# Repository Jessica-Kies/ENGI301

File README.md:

# ENGI301
Repository for Engi301 coursework

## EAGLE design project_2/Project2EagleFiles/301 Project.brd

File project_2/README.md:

For this project, the template for a PCB for Project 1 was created. The PCB is not going to be printed, this was practice in designing it. 
The first step for this was creating a library. Most of the library is based off the MISC library given by Professor Welsh. Two devices, the PocketBeagle and LED Button were created by me. For the PocketBeagle, the footprint used was created in class. I took the example symbol and split it into two symbols for used and unused ports. The footprint and two symbols were used to create the device. For the LED Button device, I needed to create the footprint and symbol, then the device. The LED Buttons aren’t connected directly to the board, so I just needed to create places for the 4 wires per button to be soldered onto the board. 
After creating the library, the schematics were made. This involved placing all the parts used onto the sheet and connecting the correct pins. The devices included the PocketBeagle, servomotor, hex display, transistor, 4 LED Buttons, buzzer, 6 fiducials, 4 mounting holes, and multiple 1k resistors. One PocketBeagle symbol has all the pins that are connected, while the other has all the unconnected pins. This allowed for better organization on the schematic.
Next, the board layout was done. The board is 4 layers. The middle layers are the ground and power planes. The top layer has the hex display and buzzer since they are visible outside the box. The bottom layer has the PocketBeagle, transistor, LED Buttons, and servomotor. The routing was then done for the layers. Checks were run to make sure there was not interference between parts.
MacroFab Costs for 48-day lead time with parts attached: 1 board: $907.06 	10 boards: $66.945	  100 boards: $26.398 	  1000 boards: $23.034

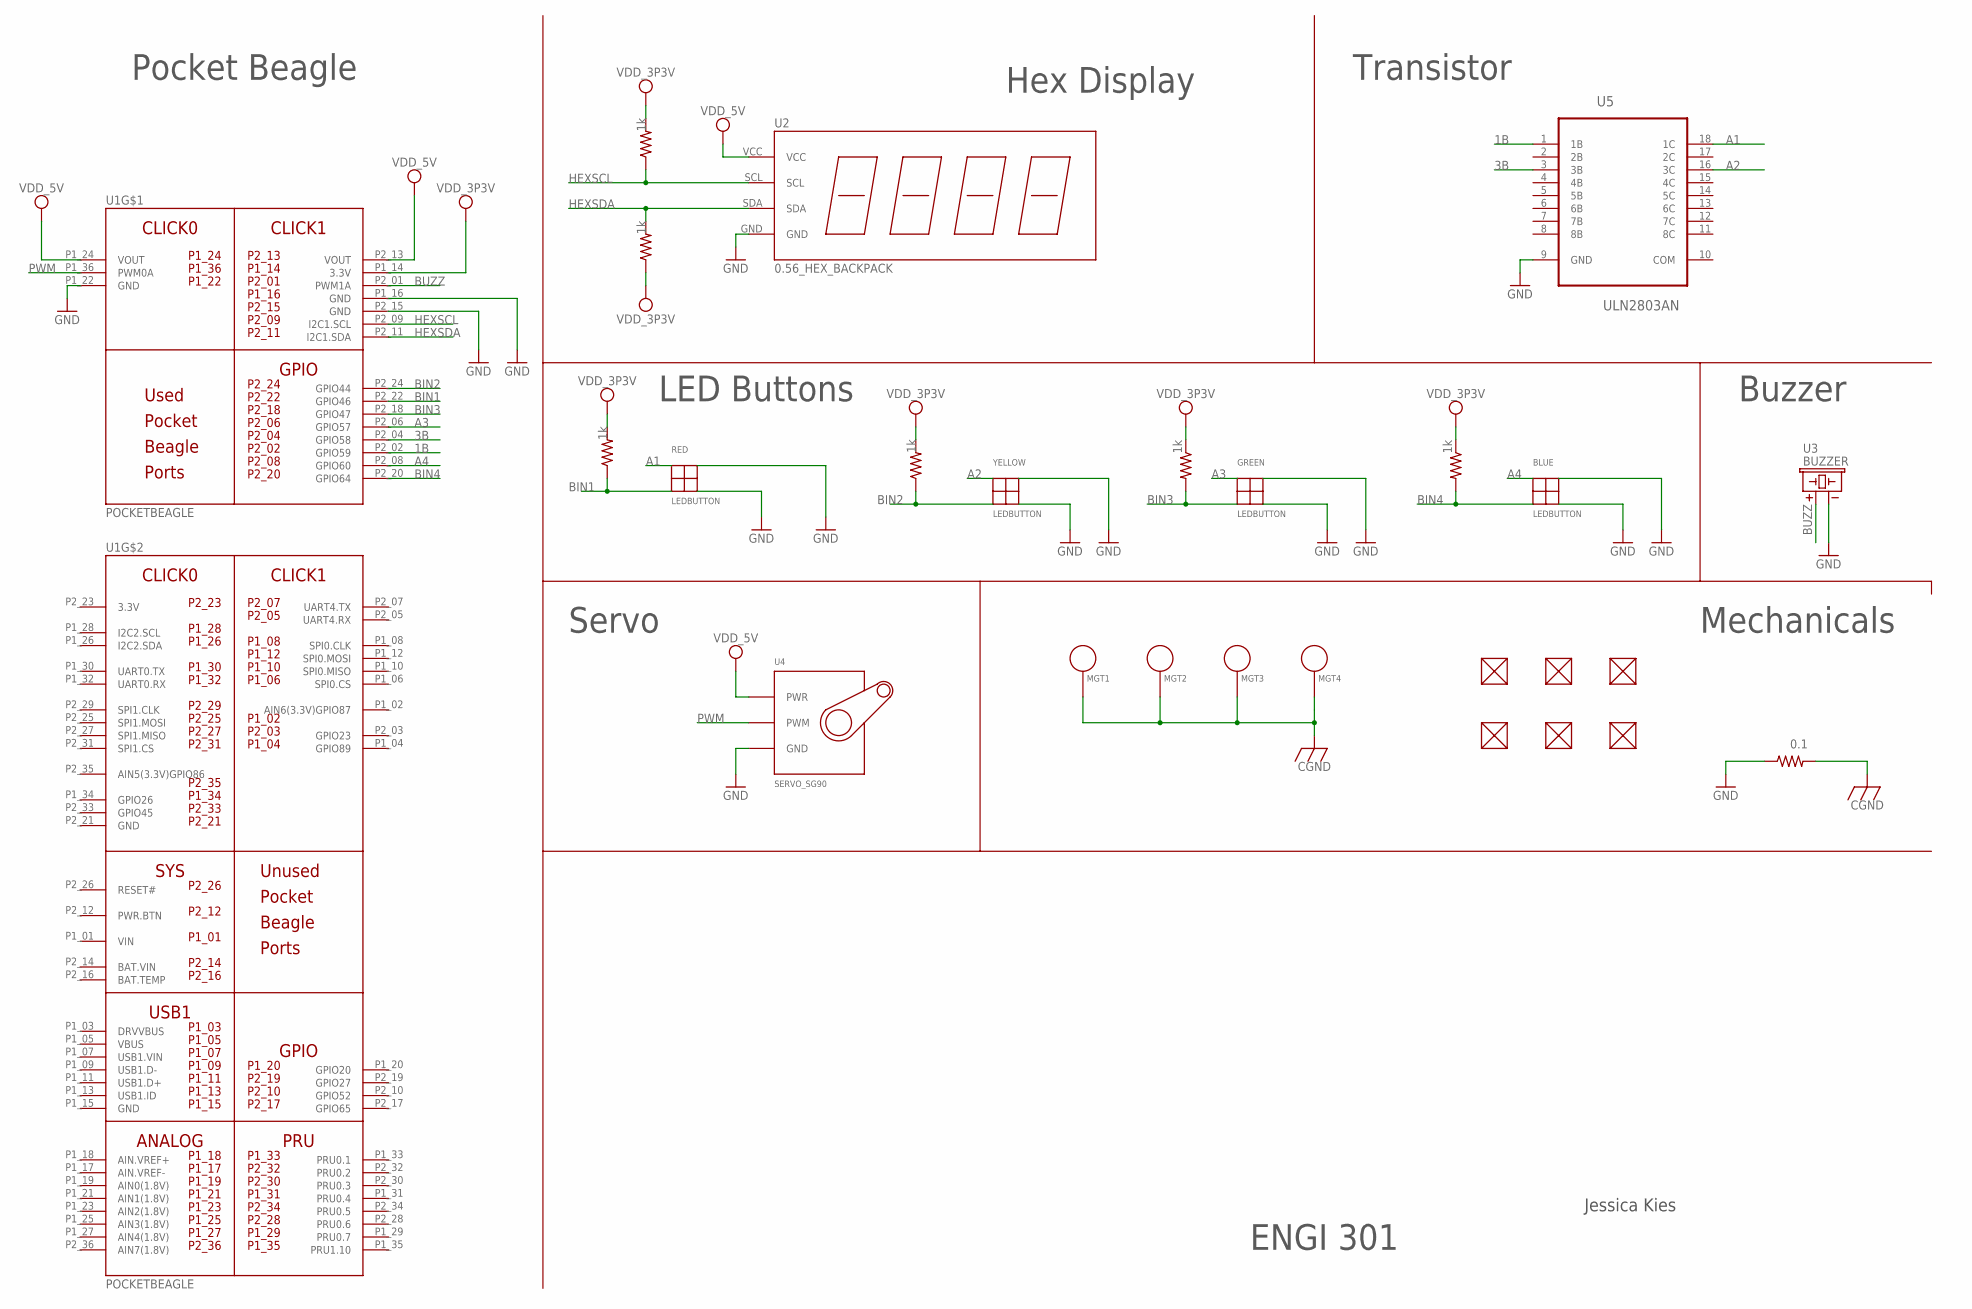
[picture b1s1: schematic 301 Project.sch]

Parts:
BLUE: LEDBUTTON
FUD1, FUD2, FUD3, FUD4, FUD5, FUD6: FIDUCIAL; FIDUCIAL_40MIL
GREEN: LEDBUTTON
MGT1, MGT2, MGT3, MGT4: MOUNTING_HOLE
R1, R2, R3, R7, R8, R9: 1k; R0402
R4: 0.1; R0402
RED: LEDBUTTON
U1: POCKETBEAGLE
U2: 0.56_HEX_BACKPACK
U3: BUZZER; BUZZER_6.5MM
U4: SERVO_SG90; SERVO-X1
U5: ULN2803AN; DIP254P762X393-18
YELLOW: LEDBUTTON

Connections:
1B: U1.P2_02 (GPIO59), U5.1 (1B)
3.3V: U1.P2_23 (3.3V)
3B: U1.P2_04 (GPIO58), U5.3 (3B)
A1: RED.ANODE, U5.18 (1C)
A2: U5.16 (3C), YELLOW.ANODE
A3: GREEN.ANODE, U1.P2_06 (GPIO57)
A4: BLUE.ANODE, U1.P2_08 (GPIO60)
BAT.VIN: U1.P2_14 (BAT.VIN)
BIN1: R3.1, RED.BIN, U1.P2_22 (GPIO46)
BIN2: R7.1, U1.P2_24 (GPIO44), YELLOW.BIN
BIN3: GREEN.BIN, R2.2, U1.P2_18 (GPIO47)
BIN4: BLUE.BIN, R1.2, U1.P2_20 (GPIO64)
BUZZ: U1.P2_01 (PWM1A), U3.+
CGND: MGT1.P$1, MGT2.P$1, MGT3.P$1, MGT4.P$1, R4.2
GND: BLUE.BOUT, BLUE.CATHODE, GREEN.BOUT, GREEN.CATHODE, R4.1, RED.BOUT, RED.CATHODE, U1.P1_16 (GND), U1.P1_22 (GND), U1.P2_15 (GND), U1.P2_21 (GND), U2.GND, U3.-, U4.GND, U5.9 (GND), YELLOW.BOUT, YELLOW.CATHODE
HEXSCL: R8.1, U1.P2_09 (I2C1.SCL), U2.SCL
HEXSDA: R9.2, U1.P2_11 (I2C1.SDA), U2.SDA
PWM: U1.P1_36 (PWM0A), U4.SIG (PWM)
VDD_3P3V: R1.1, R2.1, R3.2, R7.2, R8.2, R9.1, U1.P1_14 (3.3V)
VDD_5V: U1.P1_24 (VOUT), U1.P2_13 (VOUT), U2.VCC, U4.PWR
VIN: U1.P1_01 (VIN)

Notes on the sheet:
Pocket Beagle
Hex Display
Transistor
LED Buttons
Servo
Buzzer
Mechanicals
ENGI 301
Jessica Kies

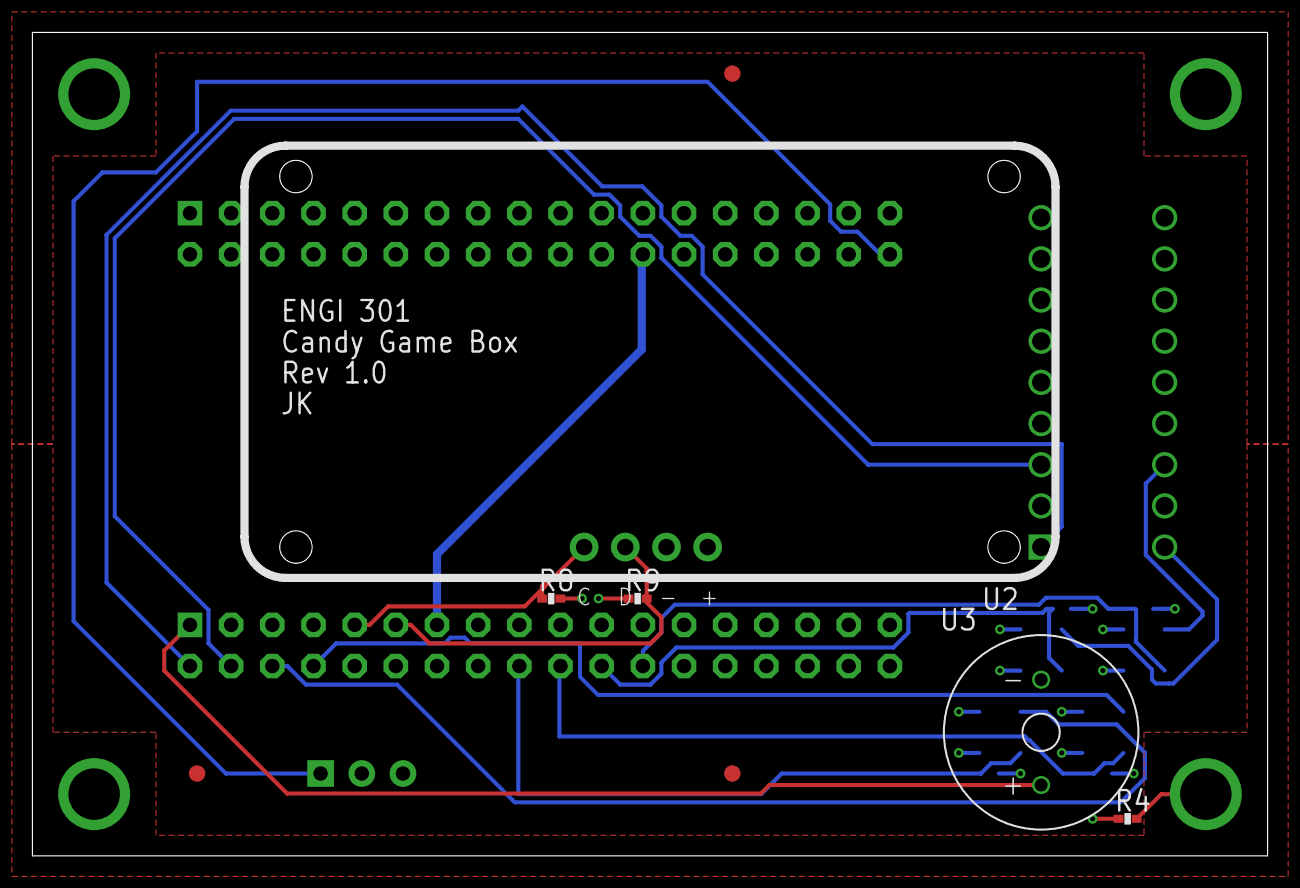
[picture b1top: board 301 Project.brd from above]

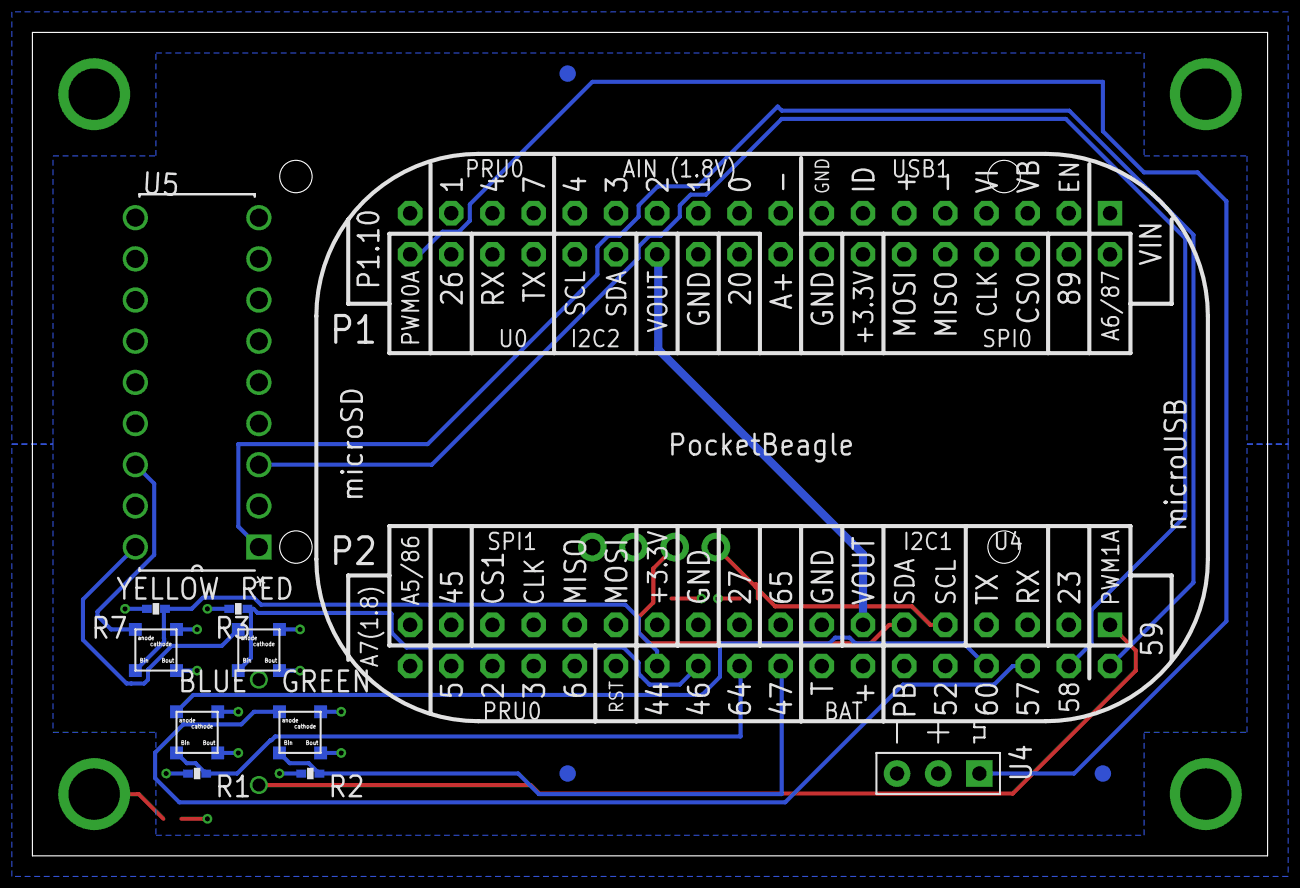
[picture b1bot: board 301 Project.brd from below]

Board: 4 copper layers, 76.2 x 50.8 mm, 26 parts (14 on the bottom side), 18 nets.

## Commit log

2021-09-16 Updating README.md
2021-09-28 Updated Simple_Calc for Homework 4
2021-10-05 Blinking LED for Assignment 4
2021-10-05 Simplified Blinking LED CODE
2021-10-06 Uploading Project Proposal
2021-10-11 create project 1
2021-10-22 LEDS light up in pattern
2021-10-22 Reads Button Presses and Returns if Correct or not
2021-10-22 Added Servo, added GPIO library to simplify code
2021-10-22 Additional functions added after win and loss, changing difficulty and can't play
2021-10-22 Final Code with Comments
2021-10-22 Final Version of Iteration 1
2021-10-22 Committing run file for game
2021-11-09 Creating README.md file
2021-11-09 Updating README
2021-11-17 Adding file via upload
2021-12-15 Add Eagle Files
2021-12-15 Adding Gerber Pictures Files
2021-12-15 Adding Schematics PDF
2021-12-15 Change BOM location
